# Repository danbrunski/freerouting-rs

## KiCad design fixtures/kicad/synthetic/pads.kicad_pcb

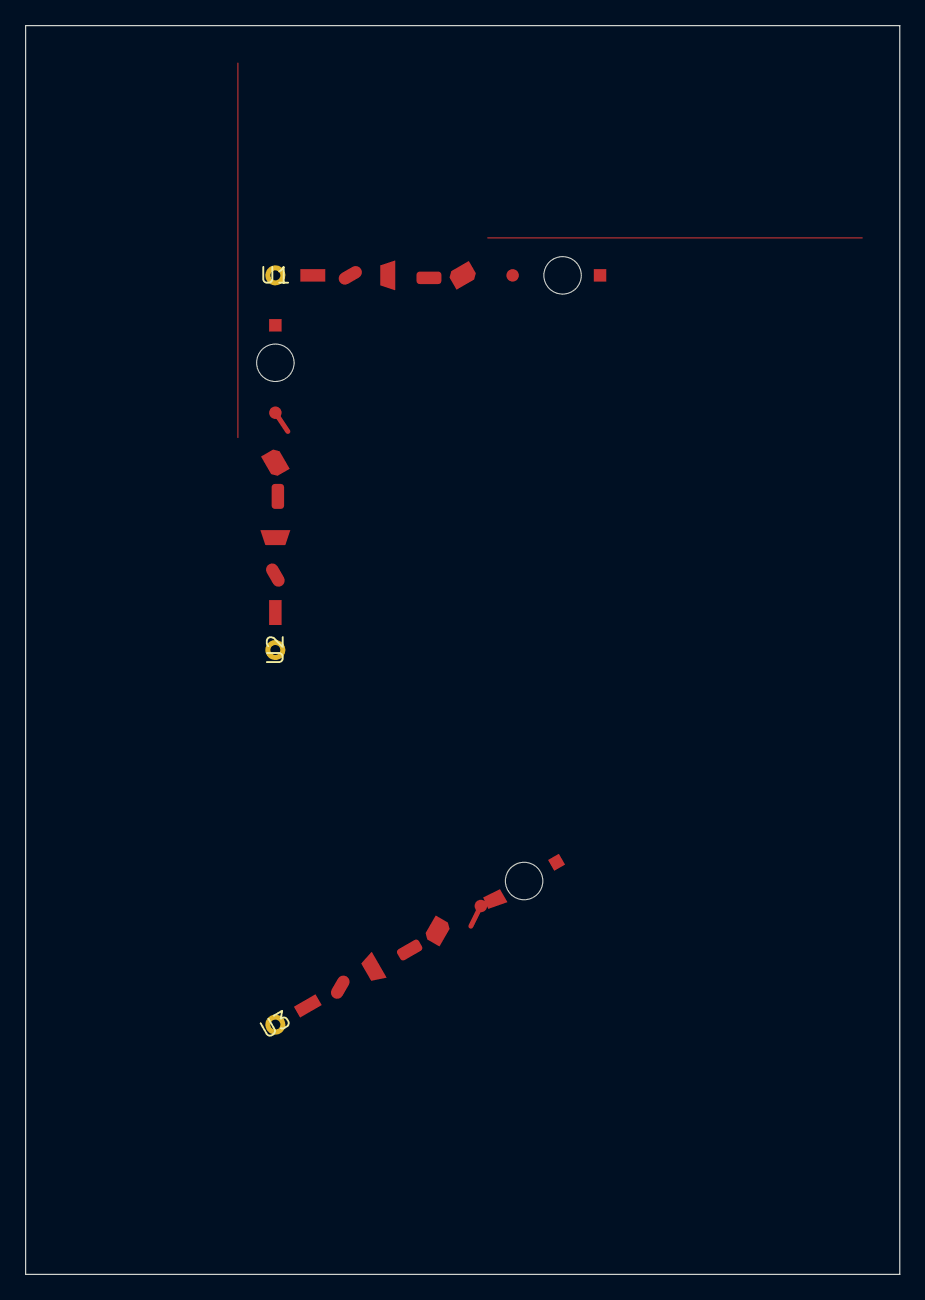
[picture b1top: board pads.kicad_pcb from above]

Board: 2 copper layers, 70.0 x 100.0 mm, 3 parts (0 on the bottom side), 3 nets, no tracks yet.

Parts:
U1, U2, U3: pads; Pads

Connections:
N1: U1.1, U1.4, U1.7, U2.1, U2.4, U2.7, U3.1, U3.4, U3.7
N2: U1.1, U1.2, U1.5, U2.1, U2.2, U2.5, U3.1, U3.2, U3.5
N3: U1.3, U1.6, U2.3, U2.6, U3.3, U3.6

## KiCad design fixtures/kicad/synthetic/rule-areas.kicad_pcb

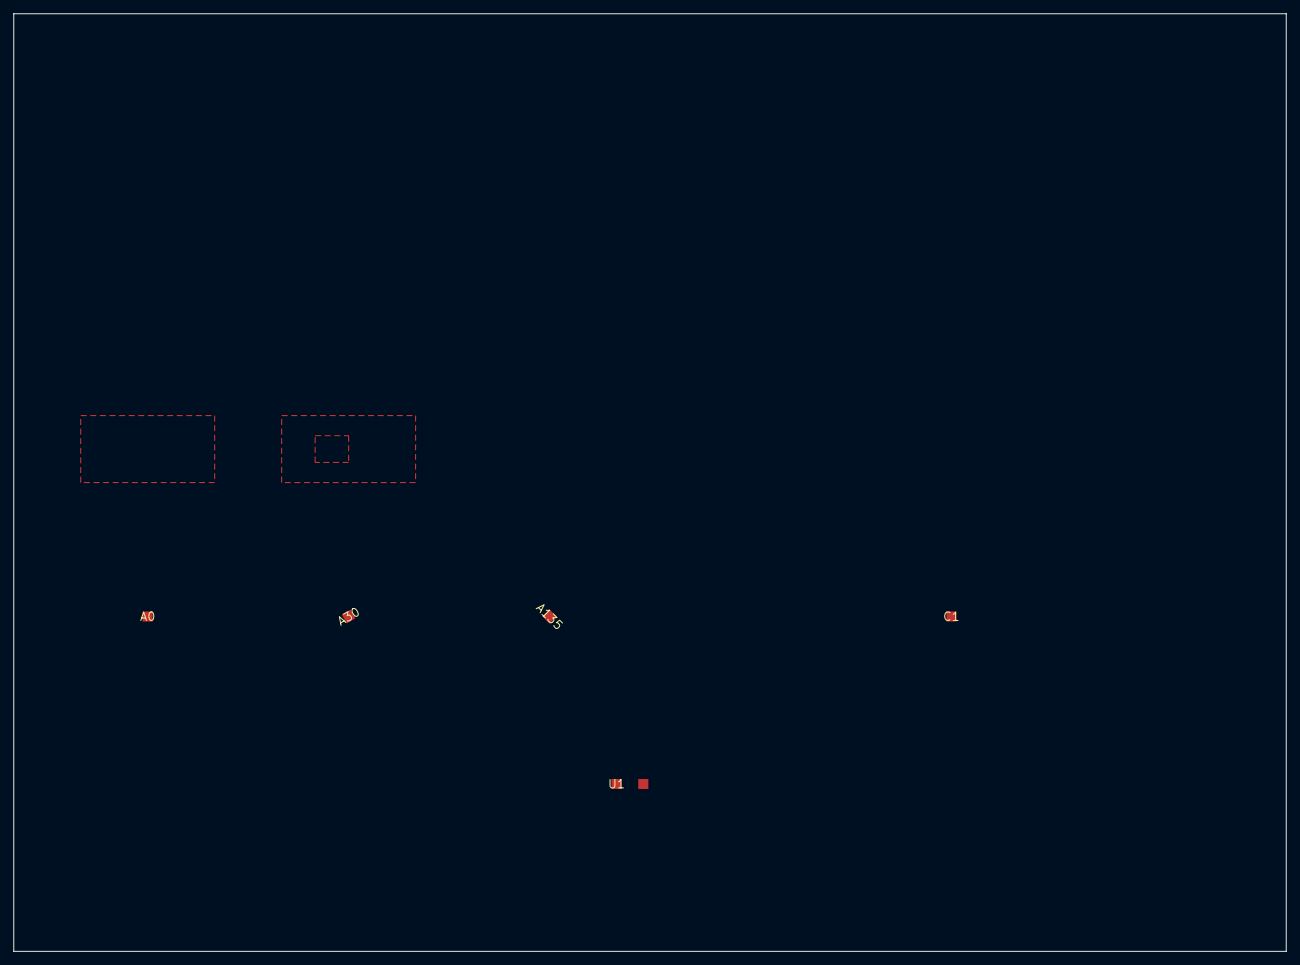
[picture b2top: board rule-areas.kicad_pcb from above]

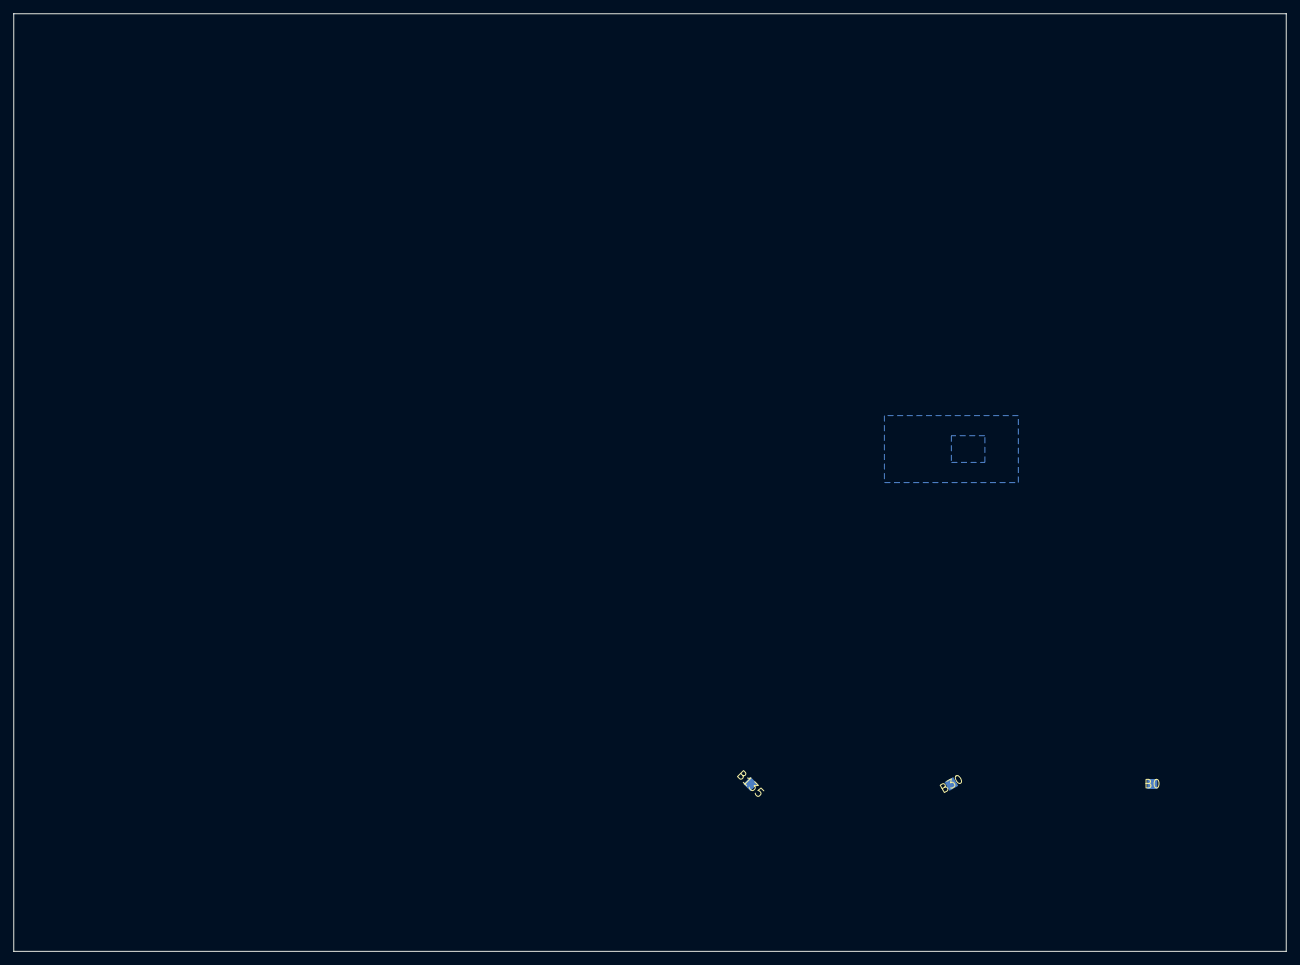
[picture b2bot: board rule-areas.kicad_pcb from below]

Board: 4 copper layers, 190.0 x 140.0 mm, 8 parts (3 on the bottom side), 2 nets, no tracks yet.

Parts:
A0, A30, A135: area; Area
B0, B30, B135: area; Area
C1: copper; Copper
U1: V; Two

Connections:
N1: A0.1, A30.1, A135.1, B0.1, B30.1, B135.1, U1.1
N2: C1.1, U1.2
